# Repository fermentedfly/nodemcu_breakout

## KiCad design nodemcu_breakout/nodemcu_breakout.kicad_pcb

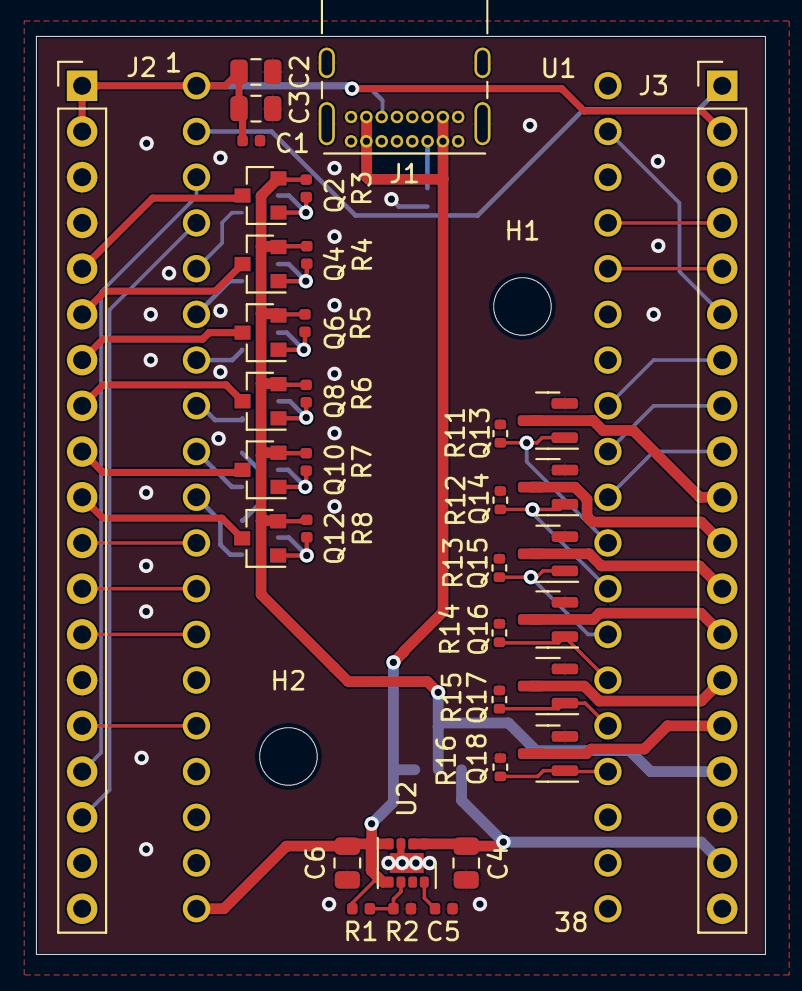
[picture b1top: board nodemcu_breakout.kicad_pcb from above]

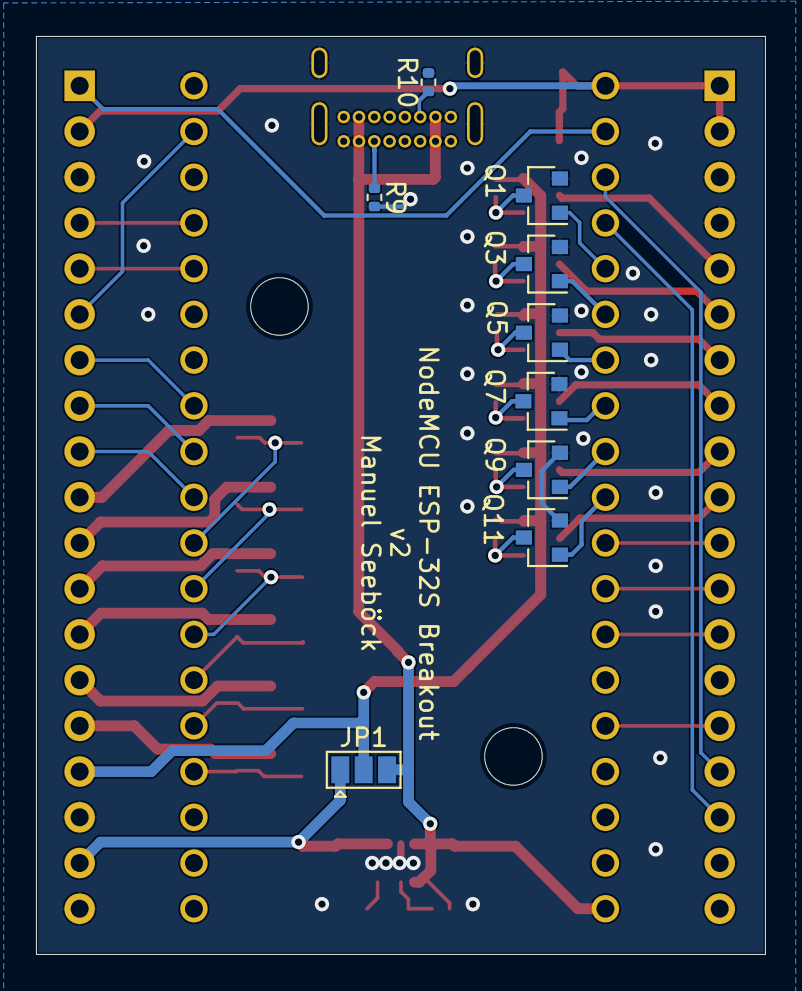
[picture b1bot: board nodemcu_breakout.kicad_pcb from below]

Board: 2 copper layers, 40.5 x 51.0 mm, 48 parts (9 on the bottom side), 52 nets.

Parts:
C1: 100n; C_0402_1005Metric
C2, C3: 100u; C_0805_2012Metric
C4: 10uF 25V; C_0805_2012Metric
C5: 3.3nF 25V; C_0402_1005Metric
C6: 22uF 16V; C_0805_2012Metric
H1, H2: MountingHole; MountingHole_3.2mm_M3
J1: USB_C_Receptacle_USB2.0; USB_C_Receptacle_GCT_USB4085
J2, J3: Conn_01x19; PinHeader_1x19_P2.54mm_Vertical
JP1: SolderJumper_3_Open; SolderJumper-3_P1.3mm_Open_Pad1.0x1.5mm
Q1, Q3, Q5, Q7, Q9, Q11: 2N7002; SOT-23
Q2, Q4, Q6, Q8, Q10, Q12: SSM3J332R; SOT-23
Q13, Q14, Q15, Q16, Q17, Q18: SSM3K336R; SOT-23
R1: 316k; R_0402_1005Metric
R2, R3, R4, R5, R6, R7, R8, R11, R12, R13, R14, R15, R16: 100k; R_0402_1005Metric
R9, R10: 5k1; R_0402_1005Metric
U1: esp32; esp-32s
U2: TPS82150; Texas_SIL0008D_MicroSiP-8-1EP_2.8x3mm_P0.65mm_EP1.1x1.9mm

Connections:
+3V3: C1.1, C2.1, C3.1, J2.1, J2.2, J3.2, U1.1 (3v3)
+5V: C6.1, J1.A4 (VBUS), J1.A9 (VBUS), J1.B4 (VBUS), J1.B9 (VBUS), JP1.3 (B), R1.1, U1.19 (5V), U2.4 (VOUT), U2.5 (VOUT)
+VDC: C4.1, J3.18, JP1.1 (A), U2.1 (EN), U2.2 (VIN)
/P12: J2.13, U1.13 (P12)
/P13: J2.15, U1.15 (P13)
/P14: J2.12, U1.12 (P14)
/P27: J2.11, U1.11 (P27)
/PWM_0: Q1.1 (G), U1.5 (P34)
/PWM_1: Q3.1 (G), U1.6 (P35)
/PWM_2: Q5.1 (G), U1.7 (P32)
/PWM_3: Q7.1 (G), U1.8 (P33)
/PWM_4: Q9.1 (G), U1.9 (P25)
/PWM_5: Q11.1 (G), U1.10 (P26)
/PWM_6: Q13.1 (G), R11.1, U1.30 (P17)
/PWM_7: Q14.1 (G), R12.1, U1.31 (P16)
/PWM_8: Q15.1 (G), R13.1, U1.32 (P4)
/PWM_9: Q16.1 (G), R14.1, U1.33 (P0)
/PWM_10: Q17.1 (G), R15.1, U1.34 (P2)
/PWM_11: Q18.1 (G), R16.1, U1.35 (P15)
/PWM_H0_OUT: J2.5, Q2.3 (D)
/PWM_H1_OUT: J2.6, Q4.3 (D)
/PWM_H2_OUT: J2.7, Q6.3 (D)
/PWM_H3_OUT: J2.8, Q8.3 (D)
/PWM_H4_OUT: J2.9, Q10.3 (D)
/PWM_H5_OUT: J2.10, Q12.3 (D)
/PWM_L0_OUT: J3.10, Q13.3 (D)
/PWM_L1_OUT: J3.11, Q14.3 (D)
/PWM_L2_OUT: J3.12, Q15.3 (D)
/PWM_L3_OUT: J3.13, Q16.3 (D)
/PWM_L4_OUT: J3.14, Q17.3 (D)
/PWM_L5_OUT: J3.15, Q18.3 (D)
/PWR_OUT: J3.16, JP1.2 (C), Q2.2 (S), Q4.2 (S), Q6.2 (S), Q8.2 (S), Q10.2 (S), Q12.2 (S), R3.1, R4.1, R5.1, R6.1, R7.1, R8.1
/SVN: J2.17, U1.4 (SVN)
/SVP: J2.16, U1.3 (SVP)
/eg_TPS82150/FB: R1.2, R2.1, U2.6 (FB)
/nRESET: J3.1, U1.2 (EN)
/spi_miso: J3.7, U1.27 (P19)
/spi_mosi: J3.6, U1.21 (P23)
/spi_nSS: J3.9, U1.29 (P5)
/spi_sck: J3.8, U1.28 (P18)
/uart_rx: J3.5, U1.24 (RX)
/uart_tx: J3.4, U1.23 (TX)
GND: C1.2, C2.2, C3.2, C4.2, C5.2, C6.2, J1.A1 (GND), J1.A12 (GND), J1.B1 (GND), J1.B12 (GND), J1.S1 (SHIELD), J2.3, J2.4, J2.14, J3.3, J3.17, J3.19, Q1.2 (S), Q3.2 (S), Q5.2 (S), Q7.2 (S), Q9.2 (S), Q11.2 (S), Q13.2 (S), Q14.2 (S), Q15.2 (S), Q16.2 (S), Q17.2 (S), Q18.2 (S), R2.2, R9.2, R10.2, R11.2, R12.2, R13.2, R14.2, R15.2, R16.2, U1.14 (GND), U1.20 (GND), U1.26 (GND), U2.3 (GND), U2.9 (GND)
unnamed: C5.1, U2.8 (SS/TR)
unnamed: J1.A5 (CC1), R9.1
unnamed: J1.B5 (CC2), R10.1
unnamed: Q1.3 (D), Q2.1 (G), R3.2
unnamed: Q3.3 (D), Q4.1 (G), R4.2
unnamed: Q5.3 (D), Q6.1 (G), R5.2
unnamed: Q7.3 (D), Q8.1 (G), R6.2
unnamed: Q9.3 (D), Q10.1 (G), R7.2
unnamed: Q11.3 (D), Q12.1 (G), R8.2

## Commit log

2020-06-19 breakout v1 done
2022-10-21 v2, added nmos pwm out
2022-10-24 kicad update
